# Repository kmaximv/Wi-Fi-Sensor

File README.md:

# Wi-Fi Sensor

Датчик температуры, влажности, давления, движения и освещенности на ESP-12F

Для управления нагрузкой есть два варианта платы. Первый вариант для низковольтной нагрузки, в моем случае это светодиодные ленты. Второй вариант для высоковольтной нагрузки (220 вольт), используемое твёрдотельное реле выдерживает ток до 8 ампер.

Все датчики и Wi-Fi модуль работают от питания 3,3V.

Плату заказывал по инструкции автора Vipeg [Ссылка](http://mysku.ru/blog/others/36157.html) , за что ему отдельное спасибо.

#### Дополнительная инфорамация на [Wiki](https://github.com/kmaximv/Wi-Fi-Sensor/wiki)

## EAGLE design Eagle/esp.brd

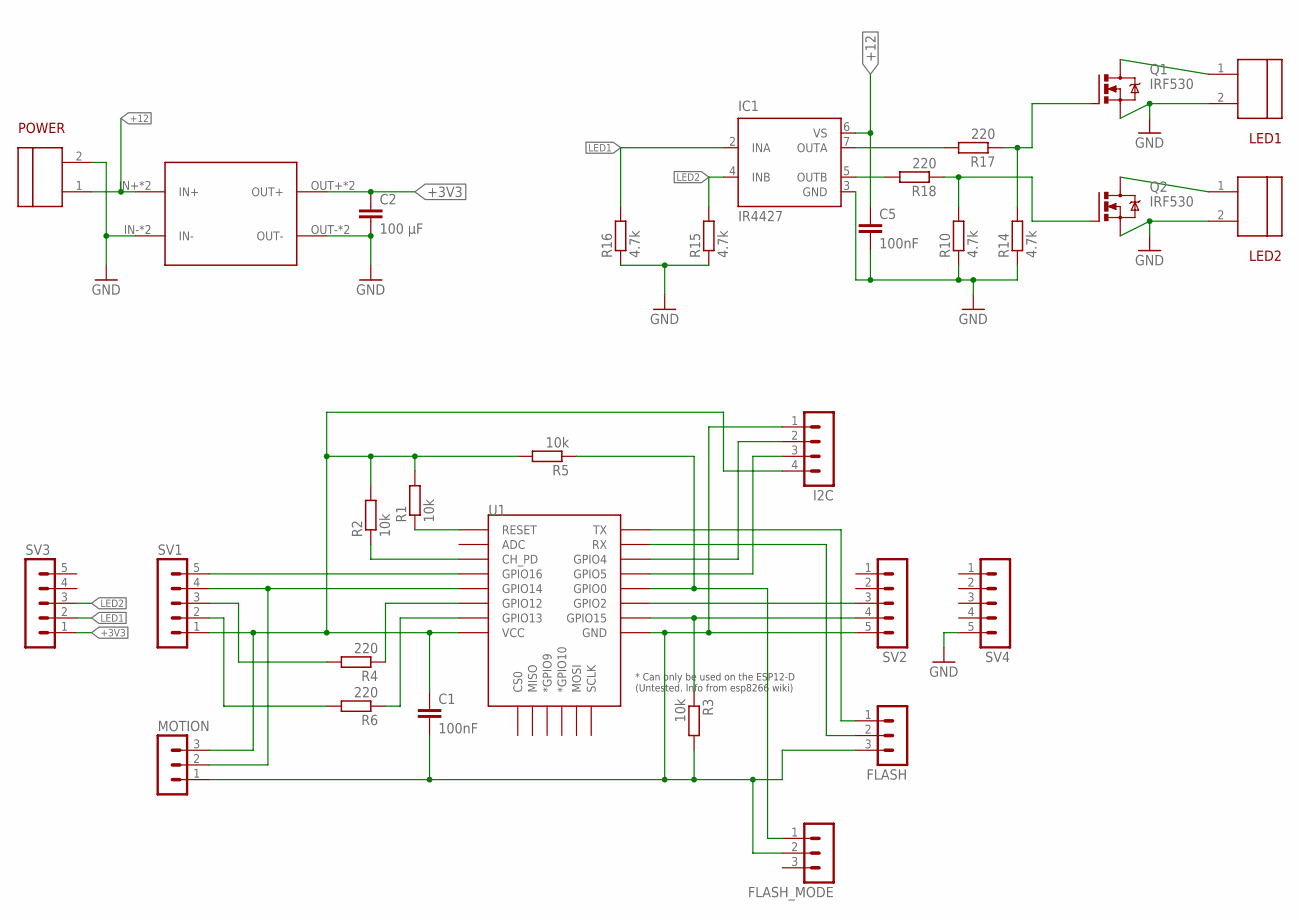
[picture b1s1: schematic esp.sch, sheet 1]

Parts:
C1, C5: 100nF; CAP-PTH-5MM
C2: 100 µF; CAP-PTH-5MM
DC-DC_3V3: DC-DC-MP1504EN
FLASH: MA03-1
FLASH_MODE: MA03-1
I2C: MA04-1
IC1: IR4427; DIL08
LED1, LED2: DG3502P; DG350
MOTION: MA03-1
POWER: DG3502P; DG350
Q1, Q2: IRF530; TO220BV
R1, R2, R3, R5: 10k; R1206
R4, R6, R17, R18: 220; R1206
R10, R14, R15, R16: 4.7k; R1206
SV1, SV2, SV3, SV4: MA05-1
U1: ESP12ESMD; ESP12E-SMD

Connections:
+3V3: C2.1, DC-DC_3V3.OUT2+ (OUT+), DC-DC_3V3.OUT+, SV3.1
+12: C5.1, DC-DC_3V3.IN2+ (IN+), DC-DC_3V3.IN+, IC1.6 (VS), POWER.1
GND: C2.2, C5.2, DC-DC_3V3.IN2- (IN-), DC-DC_3V3.IN-, DC-DC_3V3.OUT2- (OUT-), DC-DC_3V3.OUT-, IC1.3 (GND), LED1.2, LED2.2, POWER.2, Q1.S, Q2.S, R10.1, R14.1, R15.1, R16.1, SV4.5
LED1: IC1.2 (INA), R16.2, SV3.2
LED2: IC1.4 (INB), R15.2, SV3.3
MOTION_SENSOR: MOTION.2, SV1.4, U1.GPIO14
unnamed: R1.1, U1.RESET
unnamed: R2.1, U1.CH_PD
unnamed: FLASH_MODE.1, R5.1, U1.GPIO0
unnamed: R3.1, SV2.4, U1.GPIO15
unnamed: LED1.1, Q1.D
unnamed: LED2.1, Q2.D
unnamed: R6.1, U1.GPIO13
unnamed: R4.1, U1.GPIO12
unnamed: SV2.3, U1.GPIO2
unnamed: C1.1, I2C.4, MOTION.3, R1.2, R2.2, R5.2, SV1.1, U1.VCC
unnamed: R6.2, SV1.2
unnamed: R4.2, SV1.3
unnamed: SV1.5, U1.GPIO16
unnamed: FLASH.1, U1.TXD0 (TX)
unnamed: FLASH.2, U1.RXD0 (RX)
unnamed: C1.2, FLASH.3, FLASH_MODE.2, I2C.1, MOTION.1, R3.2, SV2.5, U1.GND
unnamed: IC1.5 (OUTB), R18.2
unnamed: Q2.G, R10.2, R18.1
unnamed: IC1.7 (OUTA), R17.2
unnamed: Q1.G, R14.2, R17.1
SCL: I2C.3, U1.GPIO5
SDA: I2C.2, U1.GPIO4

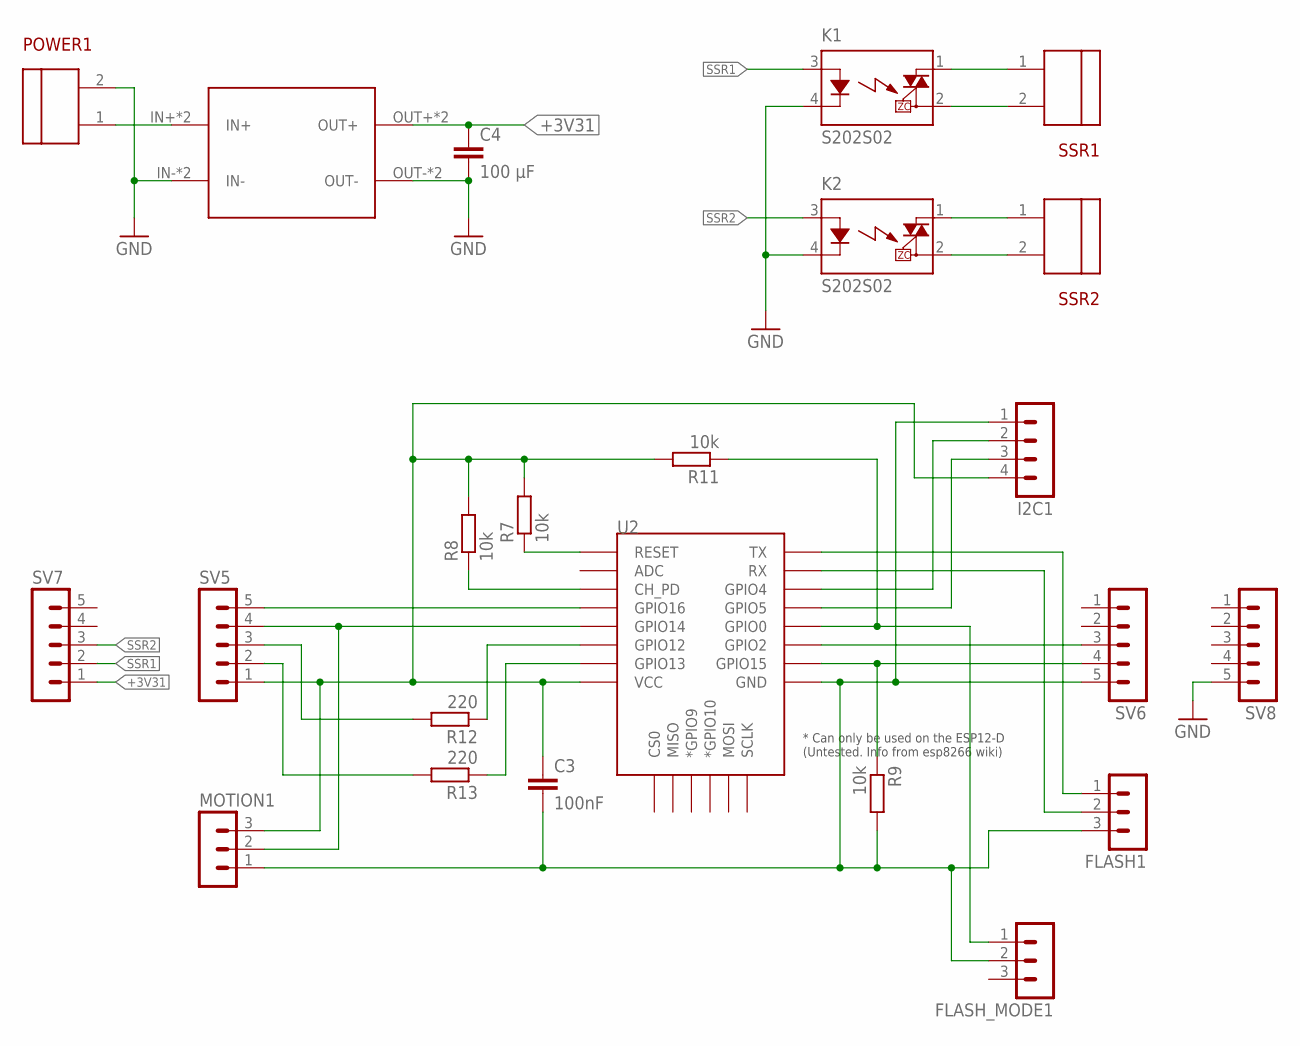
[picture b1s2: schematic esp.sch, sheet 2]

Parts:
C3: 100nF; CAP-PTH-5MM
C4: 100 µF; CAP-PTH-5MM
DC-DC_3V1: DC-DC-MP1504EN
FLASH1: MA03-1
FLASH_MODE1: MA03-1
I2C1: MA04-1
K1, K2: S202S02
MOTION1: MA03-1
POWER1: DG3502P; DG350
R7, R8, R9, R11: 10k; R1206
R12, R13: 220; R1206
SSR1, SSR2: DG3502P; DG350
SV5, SV6, SV7, SV8: MA05-1
U2: ESP12ESMD; ESP12E-SMD

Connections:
+3V31: C4.1, DC-DC_3V1.OUT2+ (OUT+), DC-DC_3V1.OUT+, SV7.1
GND1: C4.2, DC-DC_3V1.IN2- (IN-), DC-DC_3V1.IN-, DC-DC_3V1.OUT2- (OUT-), DC-DC_3V1.OUT-, K1.4 (K), K2.4 (K), POWER1.2, SV8.5
MOTION_SENSOR1: MOTION1.2, SV5.4, U2.GPIO14
unnamed: R8.1, U2.CH_PD
unnamed: FLASH_MODE1.1, R11.1, U2.GPIO0
unnamed: R7.1, U2.RESET
unnamed: R9.1, SV6.4, U2.GPIO15
unnamed: C3.1, I2C1.4, MOTION1.3, R7.2, R8.2, R11.2, SV5.1, U2.VCC
unnamed: R13.1, U2.GPIO13
unnamed: R12.1, U2.GPIO12
unnamed: R13.2, SV5.2
unnamed: R12.2, SV5.3
unnamed: SV5.5, U2.GPIO16
unnamed: FLASH1.1, U2.TXD0 (TX)
unnamed: FLASH1.2, U2.RXD0 (RX)
unnamed: C3.2, FLASH1.3, FLASH_MODE1.2, I2C1.1, MOTION1.1, R9.2, SV6.5, U2.GND
unnamed: SV6.3, U2.GPIO2
unnamed: DC-DC_3V1.IN2+ (IN+), DC-DC_3V1.IN+, POWER1.1
unnamed: K1.1 (DS1), SSR1.1
unnamed: K1.2 (DS2), SSR1.2
unnamed: K2.1 (DS1), SSR2.1
unnamed: K2.2 (DS2), SSR2.2
SCL1: I2C1.3, U2.GPIO5
SDA1: I2C1.2, U2.GPIO4
SSR1: K1.3 (A), SV7.2
SSR2: K2.3 (A), SV7.3

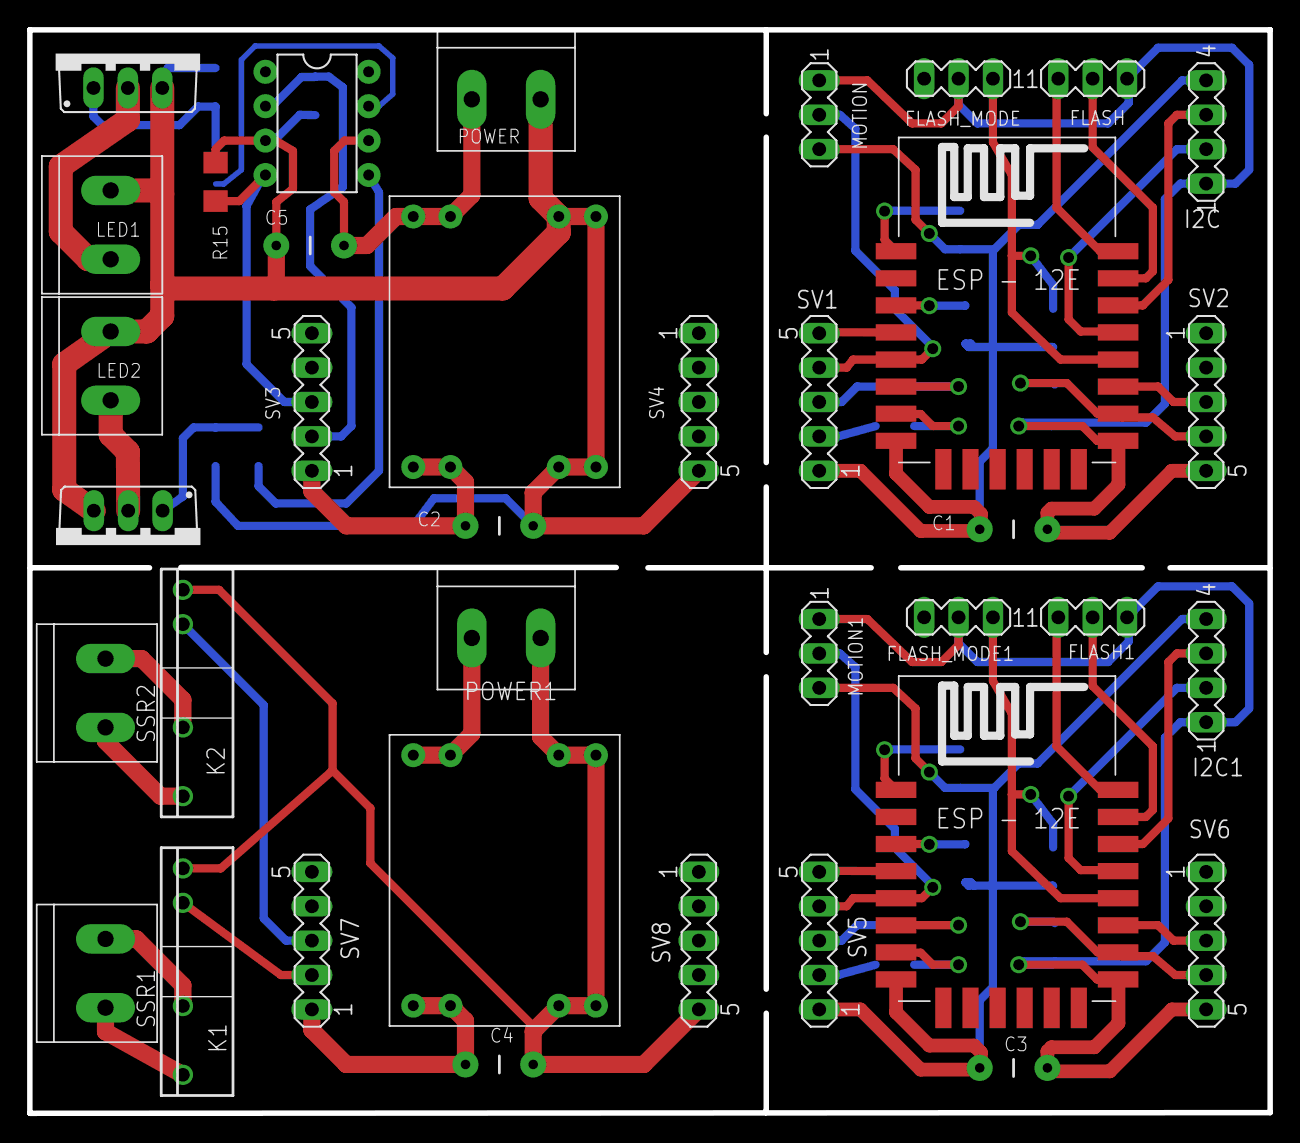
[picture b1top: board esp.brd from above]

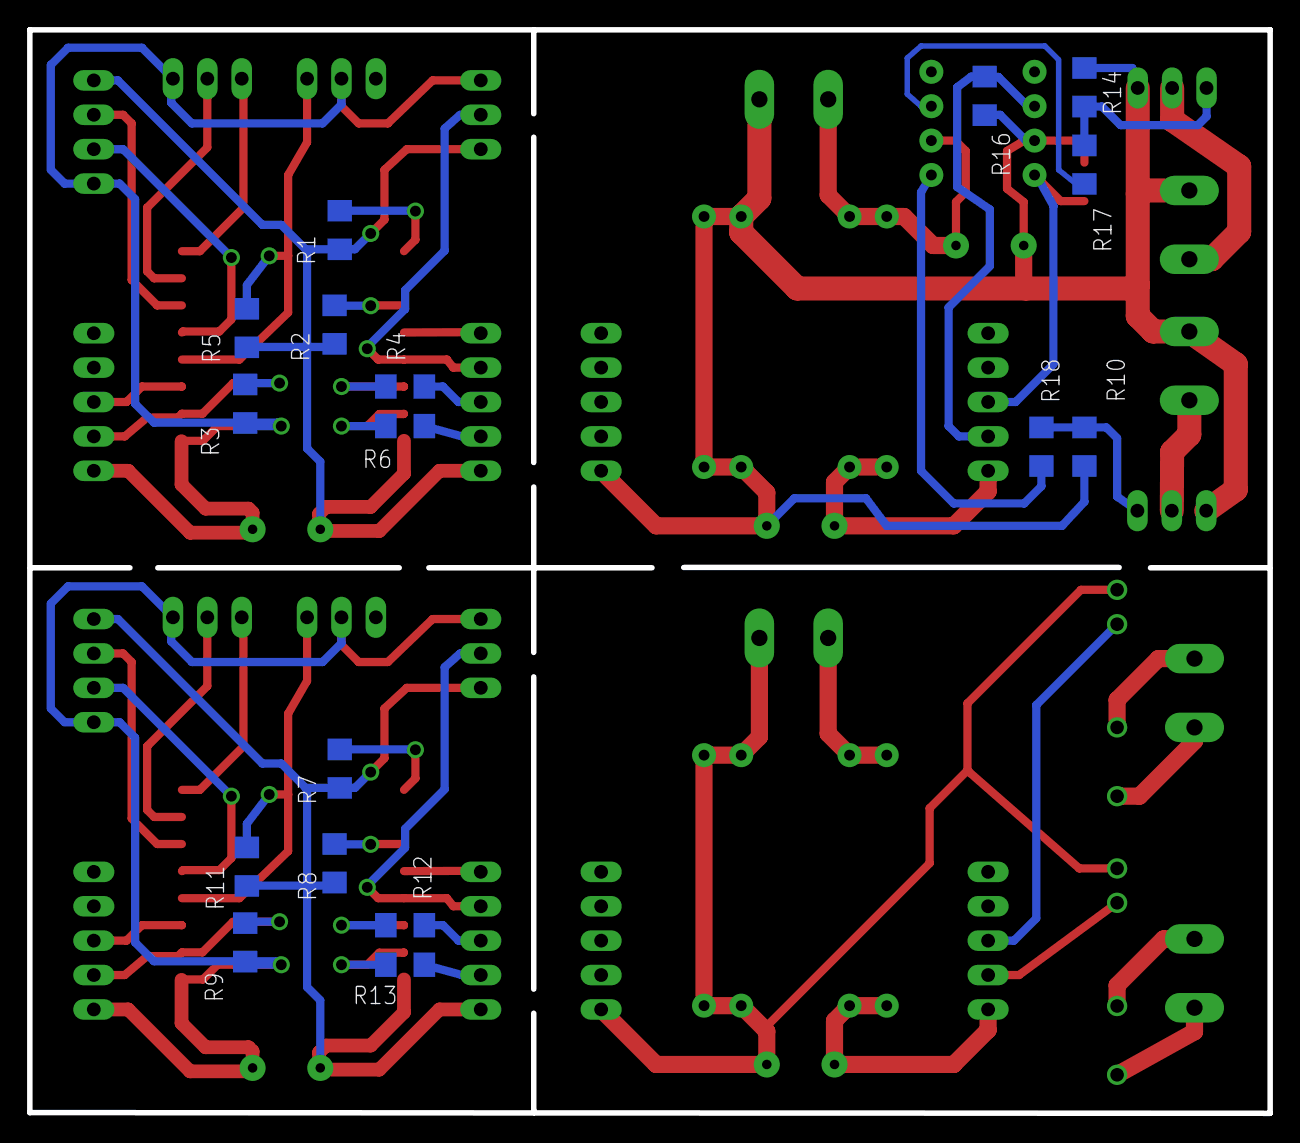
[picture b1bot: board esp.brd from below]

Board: 2 copper layers, 91.6 x 80.0 mm, 54 parts (17 on the bottom side), 54 nets.

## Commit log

2016-01-15 Add Arduino sketch
2016-01-15 Add Eagle and Gerber files
2016-01-15 Add screenshots
2016-01-15 modified README.md
2016-01-15 modified: README.md
2016-01-18 Добавлена возможность настройки статического адреса
2016-01-19 изменение сохранения настроек статического ip
2016-01-19 fix staticIpMode
2016-01-19 fix staticIpMode При сохранении страницы конфигурации пароль заменялся на звездочки. проверка пароля на наличие 8 звездочек
2016-01-21 Add OpenHab config and screens
2016-01-22 Fix: Static ip OFF
2016-01-22 cherry-picking commit ebd98c3
2016-01-22 Saving RAM using F() macro
    Conflicts:
    esp_sensor/esp_sensor.ino
2016-01-22 fix F()
2016-01-22 add file .gitignore
2016-01-22 Saving RAM using F(), add ajax update pressure
2016-01-22 fix F() for XML String
    Conflicts:
    esp_sensor/esp_sensor.ino
2016-01-22 refactoring code in esp_sensor.ino
2016-01-23 Add Ajax on web "Control Pins", add control 2 Led Strip
2016-01-23 Add Debug info and check json load data
2016-01-23 revert diff change
2016-01-26 refactoring esp_sensor.ino
2016-01-26 fix error in function MotionDetect() Ошибка вызывала перезагрузку устройства при отправке сообщения по MQTT
2016-01-27 fix json load in loadConfig()
2016-01-28 Add in web config lightOffTimer and lightOffTimer2
2016-01-28 Fix web config light_off_delay
2016-01-31 fix status on web page
2016-02-02 add ESP_UART library
2016-02-02 update func UART
2016-02-03 add parse UART command
2016-02-04 add web page Analog pins
2016-02-04 fix web page Analog pin
2016-02-06 Update readmme
2016-02-06 Fix readme
2016-02-06 Add image
2016-02-07 Add web page "Analog Pins UART"
2016-02-08 Add: Configuration MQTT server as DNS name Add: Change MQTT Port
2016-02-08 add: support MQTT user and password
2016-02-08 Add: Display NTP time
2016-02-08 Add: Display voltage on status web page
2016-02-08 Add: Web Page Greenhouse, variables of Greenhouse
2016-02-09 Fix: load config
2016-02-09 reconfigure saving values in json file
2016-02-10 fix: conflict my lib name ESP_UART.h with cores/esp8266/uart.h
2016-02-10 fix: remove excess includes in MY_ESP_UART.h
2016-02-11 changed the principle of saving data in lib json_config
2016-02-12 processing fix save config
2016-02-12 Another approach to save the configuration
2016-02-15 return to old principle save/load config
2016-02-15 return to old principle save/load config part 2
2016-02-16 return to old principle save/load config part 3
2016-02-17 return to old principle save/load config part 4
2016-02-17 Fix: Static IP mode
2016-02-17 Fix: checkbox Static_IP_Mode not save state
2016-02-18 Fix: save state checkbox Static IP Mode
2016-02-19 Fix: Empty values MQTT User and password not saved
2016-02-20 Add check load values from file /config.json
2016-02-20 add func WebServerInit()
2016-02-21 Split espconfig on wificonfig and espconfig
2016-02-22 Fix: hang device if sensor BME280 not enable
2016-02-25 Add: module ID view in main menu
2016-02-25 Add: Func MQTT Enable/Disable
2016-02-25 Add: Func NTP Time Enable/Disable, configure
2016-02-25 Fix: ntp_enable not save in config.json
2016-02-25 Fix: On/Off ntp time
2016-02-26 Fix: On/Off MQTT
2016-02-26 Add: On/Off Sensors: BME280, SHT21, BH1750, Motion Sensor
2016-02-26 Fix: Reconfigure NTP service after boot
2016-02-28 Add in Debug time load func
2016-02-28 Change Html code
2016-03-03 Add: Change Wi-Fi mode
2016-03-03 Fix: Wi-Fi mode AP resetting connect
2016-03-04 Add: Wi-Fi AP_STA configure
2016-03-04 Add: Wi-Fi AP change Channel, Auth, Speed
2016-03-04 Fix: Wi-Fi AP_STA reseting connect
2016-03-08 Fix: Wi-Fi Configure
2016-03-11 Add: Light On dependent of illumination
2016-03-11 Test: Smooth Light ON
2016-03-13 Fix: Smooth Light ON
2016-03-14 Fix: Wi-Fi Safe mode
2016-03-14 Fix: replace sta_pwd on ap_pwd
2016-03-15 Add: Configure Smooth Light ON/OFF
2016-03-15 Change Web interface
2016-03-15 Fix: Smooth Ligth Disable
2016-03-15 Change: Readme.md Add: Screenshots
2016-08-26 Add reconnect Wi-Fi every 10min, if Wi-Fi Safe Mode On
2016-09-28 Add support Energy Monitor PZEM-004
2016-09-28 Add send PZEM data to MQTT
2016-09-28 Fix for updated PZEM library
2016-09-28 Add additional conditions when sending data by MQTT
2016-10-08 Add delay startup for PZEM
2016-10-09 Fix read data for PZEM
2016-10-09 Add func for reset energy PZEM
2016-10-09 Change delays for reset energy PZEM
2016-10-15 Add #define BH1750_ON, NTP_ON
2016-10-16 Add screens and configs for PZEM
2016-10-17 Updates for new library NTPClient 3.1.0
2016-10-17 Fix mqtt callback for PZEM
2016-10-17 Update screens and configs for PZEM
2016-10-20 Refactoring code
2016-10-20 Fix func GetPzemData()
2016-10-21 Func Wifi*: refactoring code
2016-10-26 Support DHT in web interface
2016-10-26 Fix sending move detect if motion sensor disable
2016-10-26 Add: config reset by pressing a button
2016-10-27 Fix WiFi func, MQTT Subscribe
2016-10-27 Fix OpenHab configs
2016-11-04 Replace MQTT library. Part1
2016-11-04 Replace MQTT library. Part2
2016-11-04 Replace MQTT library. Part3
2016-11-05 Fix web pages
2016-11-07 Save DHT pin in Json config
2016-11-08 Changed the logic of the page PinControl
2016-11-08 Fixed Ligth Control if bh1750 sensor disable
2016-11-09 Replace library for DHT
2016-11-09 Fix MQTT auth on/off
2016-11-09 Fix read DHT Sensor data
2016-11-10 Reconfigure DEBUG messages
2016-11-10 Add debug info for DHT Sensor
2016-11-15 Another principle of the creation page
2016-11-15 Create web page <log_config>
2016-11-18 Add config save for page <Logging>
2016-11-19 Changing logs level
2016-11-19 Create web page <Console>
2016-11-20 Reconfigure Web Pages
2016-11-23 Add func for support DS18X20
2016-11-24 Add sending DS18X20 data in MQTT
2016-11-24 Fix send MQTT data for DS18X20
2016-11-24 Add #ifdef DS18X20_ON
2016-11-25 Rewrite func Fading
2016-11-27 Fix NTP Update. Need to update library NtpClient
2016-11-27 Small refactoring code
2016-12-08 Fix: Error if Connecting to MQTT false
2016-12-18 Add support MH-Z19 Sensor
2016-12-19 Test support display 1602 I2C
2016-12-23 Added Encoder support
2017-01-02 Updated web pages /wificonf /scan /mqttconf /ntpconf
2017-01-02 Fix WiFi connect
2017-01-03 Added SPIFFS Editor
2017-01-03 Fix HTTP Head
2017-01-11 Small fixes
2017-01-11 Fixed loadinig page </wificonf>
2017-01-11 Rename wifi.html -> wifi.htm
2017-01-11 Added Wire.h and favicon.ico
2017-01-11 Fixed NTP Client connecting
2017-01-11 Added Arduino libraries
2017-01-21 Fix MQTT Publish data for DS18X20
2017-01-22 Fix DS18x20 get data
2017-02-02 Change movement func.
    По MQTT теперь отправляется 0\1 вместо ON\OFF
    Добавил отправку сообщения при прекращении движения (0)
2017-03-22 Срабатывание для обеих ламп
2017-03-23 Added: Boiler control Added: Test I2C LCD support Fix: Hang on web page <wificonf>
2017-04-26 Issue 32 Added check PZEM alive
2017-04-27 Issue: 32 All PZEM data change to "none"
2017-04-28 Issue: 32 Fix: sending "none" in MQTT
2017-05-16 add ESP32 boards
    Попробуем добавить поддержку ESP32, пока что с помощью переменной ESP32
